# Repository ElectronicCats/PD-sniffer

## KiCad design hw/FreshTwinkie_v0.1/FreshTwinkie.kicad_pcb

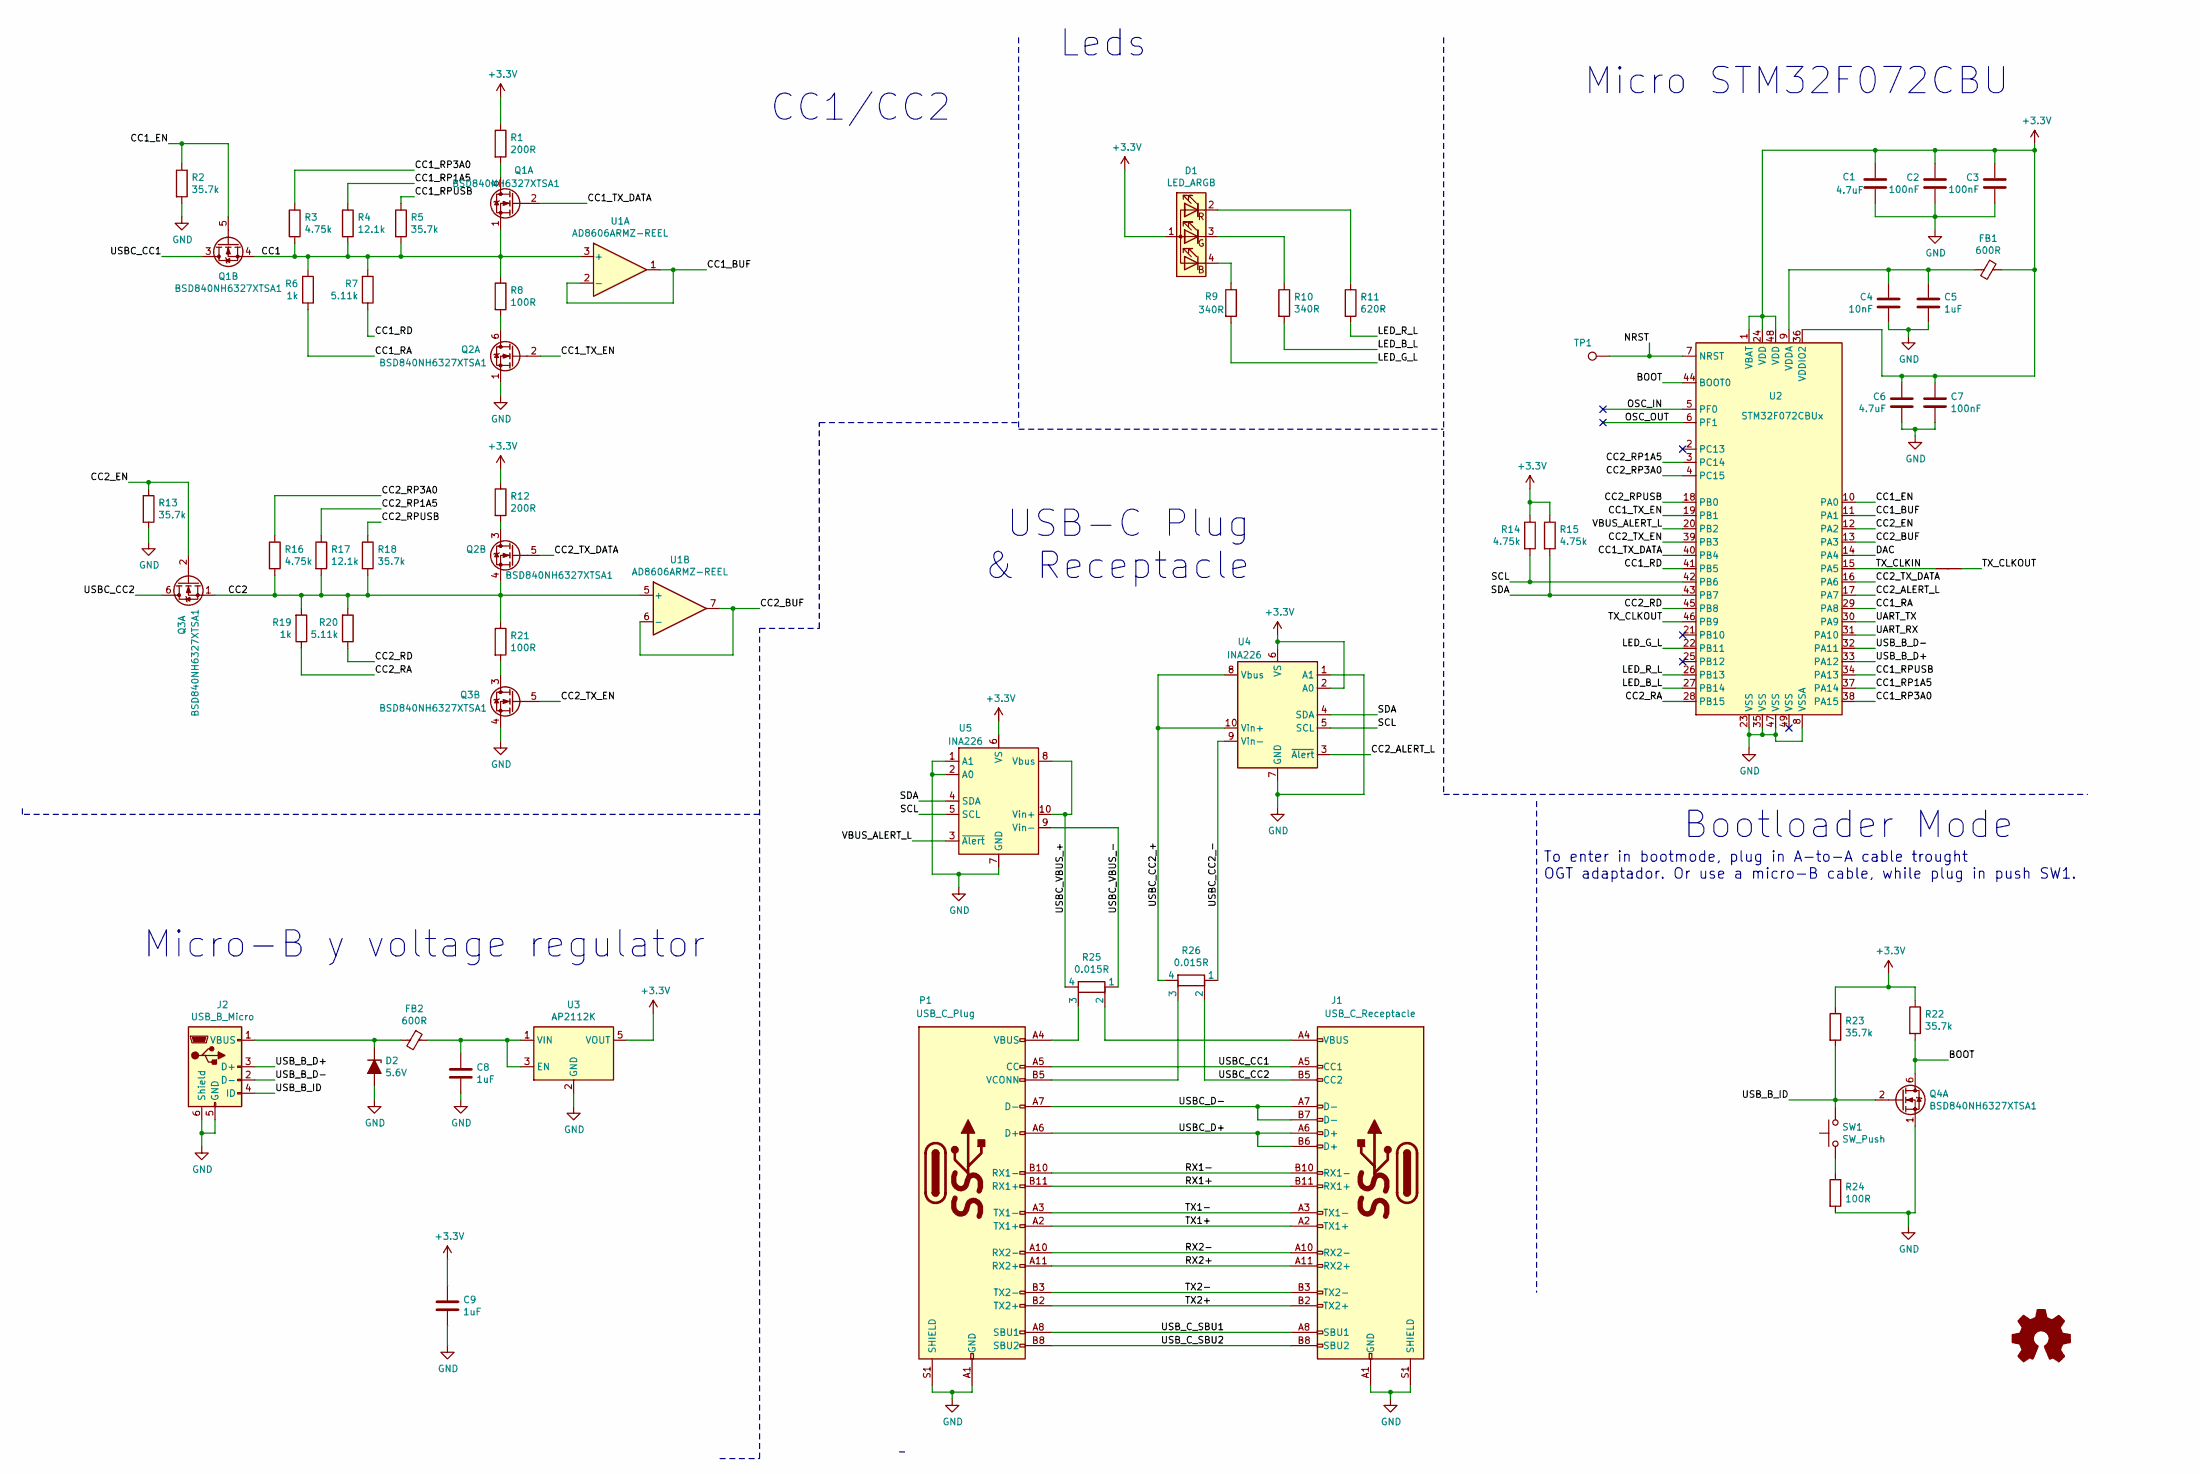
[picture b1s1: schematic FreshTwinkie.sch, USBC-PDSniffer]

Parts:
C1, C6: 4.7uF; C_0603_1608Metric
C2, C3, C7: 100nF; C_0603_1608Metric
C4: 10nF; C_0603_1608Metric
C5, C8, C9: 1uF; C_0603_1608Metric
D1: LED_ARGB; LED_Cree-PLCC4_3.2x2.8mm_CCW
D2: 5.6V; D_SOD-123
FB1, FB2: 600R; L_0603_1608Metric
J1: USB_C_Receptacle; USB_C_Receptacle_Amphenol_12401610E4-2A
J2: USB_B_Micro; U254051N4BH806
NT1: Net-Tie_2; NetTie-2_SMD_Pad0.5mm
P1: USB_C_Plug; JAE_DX07P024MJ1R1500
Q1, Q2, Q3, Q4: BSD840NH6327XTSA1; SOT-363_SC-70-6
R1, R12: 200R; R_0603_1608Metric
R2, R5, R13, R18, R22, R23: 35.7k; R_0603_1608Metric
R3, R14, R15, R16: 4.75k; R_0603_1608Metric
R4, R17: 12.1k; R_0603_1608Metric
R6, R19: 1k; R_0603_1608Metric
R7, R20: 5.11k; R_0603_1608Metric
R8, R21, R24: 100R; R_0603_1608Metric
R9, R10: 340R; R_0603_1608Metric
R11: 620R; R_0603_1608Metric
R25, R26: 0.015R; 4W_R_1206
SW1: SW_Push; C455281
TP1: TestPoint; TestPoint_Pad_D1.5mm
U1: AD8606ARMZ-REEL; MSOP-8_3x3mm_P0.65mm
U2: STM32F072CBUx; QFN50P700X700X60-49N
U3: AP2112K; SOT-23-5
U4, U5: INA226; VSSOP-10_3x3mm_P0.5mm

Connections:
+3V3: C1.1, C2.1, C3.1, C6.1, C7.1, C9.1, D1.1 (A), FB1.1, R1.1, R12.1, R14.1, R15.1, R22.1, R23.1, U2.1 (VBAT), U2.24 (VDD), U2.36 (VDDIO2), U2.48 (VDD), U3.5 (VOUT), U4.2 (A0), U4.6 (VS), U5.6 (VS)
/BOOT: Q4.6 (D), R22.2, U2.44 (BOOT0)
/CC1: Q1.1 (S), Q1.4 (S), R3.2, R4.2, R5.2, R6.2, R7.2, R8.1, U1.3 (+)
/CC1_BUF: U1.1, U1.2 (-), U2.11 (PA1)
/CC1_EN: Q1.5 (G), R2.1, U2.10 (PA0)
/CC1_RA: R6.1, U2.29 (PA8)
/CC1_RD: R7.1, U2.41 (PB5)
/CC1_RP1A5: R4.1, U2.37 (PA14)
/CC1_RP3A0: R3.1, U2.38 (PA15)
/CC1_RPUSB: R5.1, U2.34 (PA13)
/CC1_TX_DATA: Q1.2 (G), U2.40 (PB4)
/CC1_TX_EN: Q2.2 (G), U2.19 (PB1)
/CC2: Q2.4 (S), Q3.1 (S), R16.2, R17.2, R18.2, R19.2, R20.2, R21.1, U1.5 (+)
/CC2_ALERT_L: U2.17 (PA7), U4.3 (~Alert~)
/CC2_BUF: U1.6 (-), U1.7, U2.13 (PA3)
/CC2_EN: Q3.2 (G), R13.1, U2.12 (PA2)
/CC2_RA: R19.1, U2.28 (PB15)
/CC2_RD: R20.1, U2.45 (PB8)
/CC2_RP1A5: R17.1, U2.3 (PC14)
/CC2_RP3A0: R16.1, U2.4 (PC15)
/CC2_RPUSB: R18.1, U2.18 (PB0)
/CC2_TX_DATA: Q2.5 (G), U2.16 (PA6)
/CC2_TX_EN: Q3.5 (G), U2.39 (PB3)
/DAC: U2.14 (PA4)
/LED_B_L: R10.2, U2.27 (PB14)
/LED_G_L: R9.2, U2.22 (PB11)
/LED_R_L: R11.2, U2.26 (PB13)
/NRST: TP1.1, U2.7 (NRST)
/OSC_IN: U2.5 (PF0)
/OSC_OUT: U2.6 (PF1)
/RX1+: J1.B11 (RX1+), P1.B11 (RX1+)
/RX1-: J1.B10 (RX1-), P1.B10 (RX1-)
/RX2+: J1.A11 (RX2+), P1.A11 (RX2+)
/RX2-: J1.A10 (RX2-), P1.A10 (RX2-)
/SCL: R14.2, U2.42 (PB6), U4.5 (SCL), U5.5 (SCL)
/SDA: R15.2, U2.43 (PB7), U4.4 (SDA), U5.4 (SDA)
/TX1+: J1.A2 (TX1+), P1.A2 (TX1+)
/TX1-: J1.A3 (TX1-), P1.A3 (TX1-)
/TX2+: J1.B2 (TX2+), P1.B2 (TX2+)
/TX2-: J1.B3 (TX2-), P1.B3 (TX2-)
/TX_CLKIN: NT1.1, U2.15 (PA5)
/TX_CLKOUT: NT1.2, U2.46 (PB9)
/UART_RX: U2.31 (PA10)
/UART_TX: U2.30 (PA9)
/USBC_CC1: J1.A5 (CC1), P1.A5 (CC), Q1.3 (D)
/USBC_CC2: J1.B5 (CC2), Q3.6 (D), R26.2
/USBC_CC2_+: R26.4, U4.8 (Vbus), U4.10 (Vin+)
/USBC_CC2_-: R26.1, U4.9 (Vin-)
/USBC_D+: J1.A6 (D+), J1.B6 (D+), P1.A6 (D+)
/USBC_D-: J1.A7 (D-), J1.B7 (D-), P1.A7 (D-)
/USBC_VBUS_+: R25.4, U5.8 (Vbus), U5.10 (Vin+)
/USBC_VBUS_-: R25.1, U5.9 (Vin-)
/USB_B_D+: J2.3 (D+), U2.33 (PA12)
/USB_B_D-: J2.2 (D-), U2.32 (PA11)
/USB_B_ID: J2.4 (ID), Q4.2 (G), R23.2, SW1.2
/USB_C_SBU1: J1.A8 (SBU1), P1.A8 (SBU1)
/USB_C_SBU2: J1.B8 (SBU2), P1.B8 (SBU2)
/VBUS_ALERT_L: U2.20 (PB2), U5.3 (~Alert~)
GND: C1.2, C2.2, C3.2, C4.2, C5.2, C6.2, C7.2, C8.2, C9.2, D2.2 (A), J1.A1 (GND), J1.A12 (GND), J1.B1 (GND), J1.B12 (GND), J1.S1 (SHIELD), J2.5 (GND), J2.6 (Shield), P1.A1 (GND), P1.A12 (GND), P1.B1 (GND), P1.B12 (GND), P1.S1 (SHIELD), P1.S3, P1.S4, Q2.1 (S), Q3.4 (S), Q4.1 (S), R2.2, R13.2, R24.2, U2.8 (VSSA), U2.23 (VSS), U2.35 (VSS), U2.47 (VSS), U3.2 (GND), U4.1 (A1), U4.7 (GND), U5.1 (A1), U5.2 (A0), U5.7 (GND)
unnamed: C4.1, C5.1, FB1.2, U2.9 (VDDA)
unnamed: C8.1, FB2.1, U3.1 (VIN), U3.3 (EN)
unnamed: D1.2 (RK), R11.1
unnamed: D1.3 (GK), R10.1
unnamed: D1.4 (BK), R9.1
unnamed: D2.1 (K), FB2.2, J2.1 (VBUS)
unnamed: J1.A4 (VBUS), J1.A9 (VBUS), J1.B4 (VBUS), J1.B9 (VBUS), R25.2
unnamed: P1.A4 (VBUS), P1.A9 (VBUS), P1.B4 (VBUS), P1.B9 (VBUS), R25.3
unnamed: P1.B5 (VCONN), R26.3
unnamed: Q1.6 (D), R1.2
unnamed: Q2.3 (D), R12.2
unnamed: Q2.6 (D), R8.2
unnamed: Q3.3 (D), R21.2
unnamed: R24.1, SW1.1

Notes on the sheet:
Bootloader Mode
Micro STM32F072CBU
To enter in bootmode, plug in A-to-A cable trought OGT adaptador. Or use a micro-B cable, while plug in push SW1.
Leds
USB-C Plug & Receptacle
CC1/CC2
Micro-B y voltage regulator

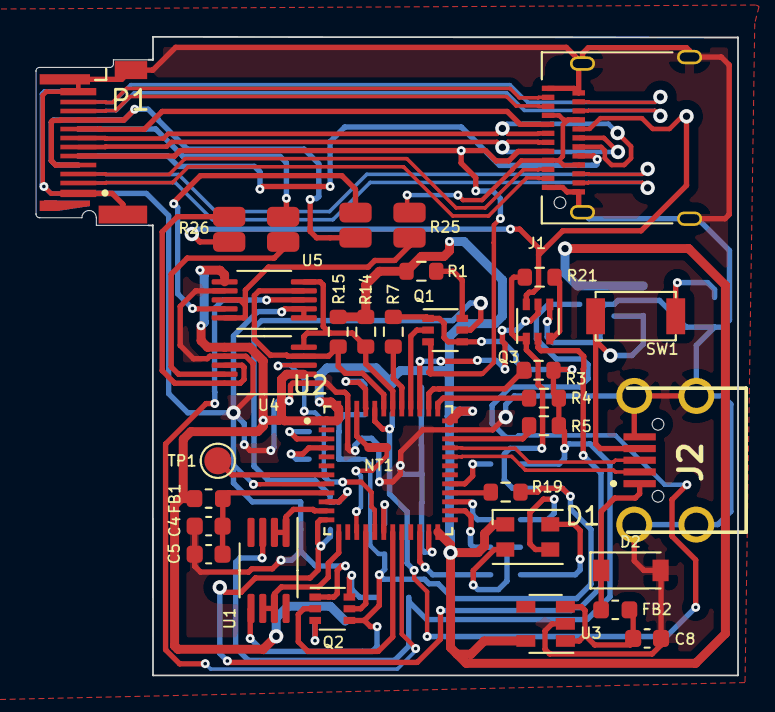
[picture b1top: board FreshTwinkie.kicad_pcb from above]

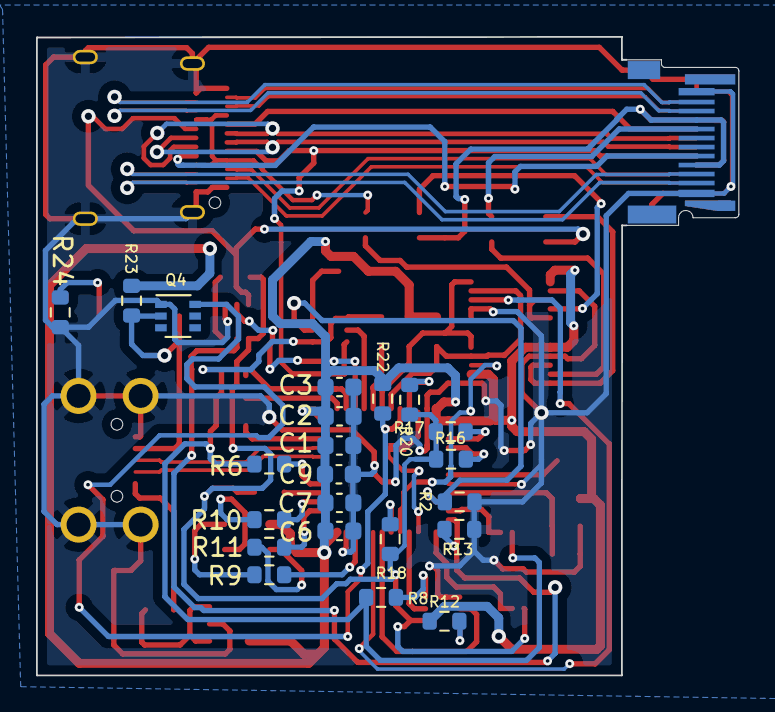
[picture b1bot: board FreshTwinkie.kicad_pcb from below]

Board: 2 copper layers, 39.0 x 35.5 mm, 54 parts (22 on the bottom side), 68 nets.

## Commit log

2021-02-24 changeFootprintMicro
2021-02-24 Redesign schematic
2021-02-24 ChangePinsMicro
2021-02-25 changeLEDRvalor
2021-02-25 generalchanges
2021-02-25 addPNdevicesPT1
2021-02-26 addfootprints&PN
2021-02-26 allcomponentsready&boom
2021-03-01 ChangeFootprintUSBCFemale
2021-03-01 changeUSBCReceptacle
2021-03-02 addnewfootprintUSBC
2021-03-02 change0805into0603
2021-03-02 switchINA260&RShunt
2021-03-03 schChanged
2021-03-03 0805into0402components
2021-03-04 Revert "start2LPCB"
    This reverts commit 90d5656826f9e90386a37f7e195560d74b09979e.
2021-03-04 start2LPCB
2021-03-04 simplechange
2021-03-04 change0402into0603
2021-03-04 usbmicroB&regulatorReady
2021-03-06 components_place
2021-03-08 routingV1
2021-03-09 routingV1.1
2021-03-09 routingUSBCP&R
2021-03-09 routingUSBCP&Rcont
2021-03-09 routingSW&Boot
2021-03-10 routingC6-9
2021-03-10 routingC4-5,FB1
2021-03-10 changeINA231forINA226
2021-03-10 changesizeofPCB&routing
2021-03-11 newroutingUSBC
2021-03-11 routeU1-5toMc
2021-03-11 routeR1&R8
2021-03-12 changeUSB-CReceptacle
2021-03-12 RearrengePCB
2021-03-12 routeResistorShout
2021-03-13 routeGND
2021-03-13 routeUSBCR&P
2021-03-13 RearrengeR6,9,10,11
2021-03-13 routingRShunttoUSBC
2021-03-13 routeFinished
2021-03-13 changeLanguagesch
2021-03-16 changeNameProjectshc
2021-03-16 correctComponentsPN
2021-03-16 chngComponentOOS
2021-03-16 addBOOMw/price
2021-03-29 changeRoute
